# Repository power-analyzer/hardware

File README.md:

# Hardware

This is the hardware and microcontroller software component of Ryan Rabello and Nathan Zimmerly's senior project.

## Getting Started

The PCB folder is a KiCAD project. Once this is done, 

## Prerequisites

KiCAD and PlatformIO using either Visual Studio Code or Atom.

## Authors

Nathan Zimmerly and Ryan Rabello.

## Acknowledgments

OpenEnergyMonitor

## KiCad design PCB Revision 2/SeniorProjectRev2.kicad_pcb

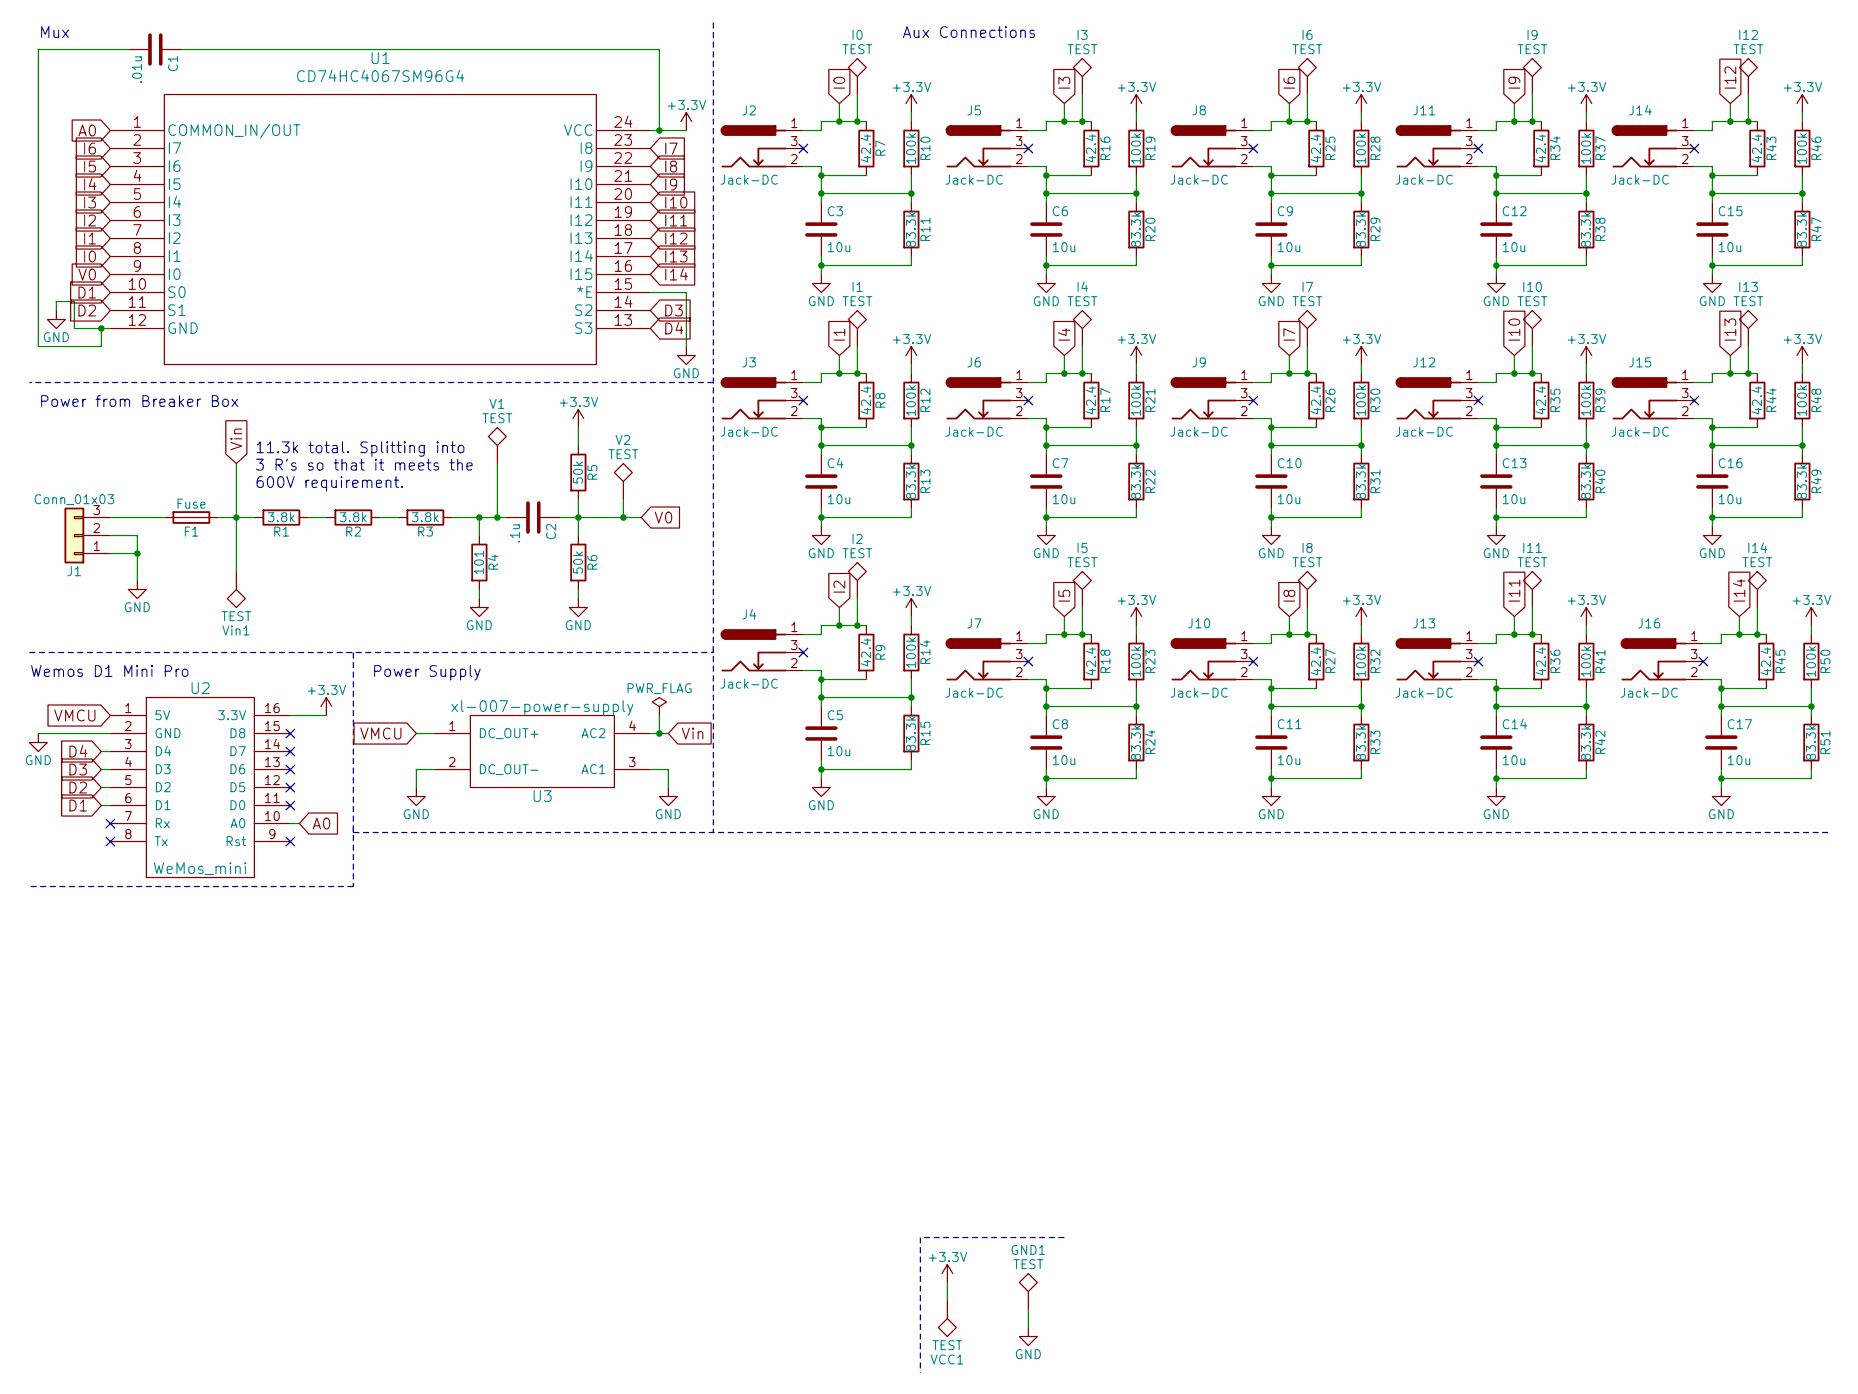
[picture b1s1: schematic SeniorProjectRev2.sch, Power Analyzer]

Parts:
C1: .01u; C_0805
C2: .1u; C_0805
C3, C4, C5, C6, C7, C8, C9, C10, C11, C12, C13, C14, C15, C16, C17: 10u; C_0805
F1: Fuse; fuse-rev2
GND1: TEST; Measurement_Point_Round-TH_Small
I0, I1, I2, I3, I4, I5, I6, I7, I8, I9, I10, I11, I12, I13, I14: TEST; Measurement_Point_Round-TH_Small
J1: Conn_01x03; CONN_TERM_BLOCK
J2, J3, J4, J5, J6, J7, J8, J9, J10, J11, J12, J13, J14, J15, J16: Jack-DC; AUDIO-JACK-TRRS-SMD-2
R1, R2, R3: 3.8k; R_0805
R4: 101; R_0805
R5, R6: 50k; R_0805
R7, R8, R9, R16, R17, R18, R25, R26, R27, R34, R35, R36, R43, R44, R45: 42.4; R_0805
R10, R12, R14, R19, R21, R23, R28, R30, R32, R37, R39, R41, R46, R48, R50: 100k; R_0805
R11, R13, R15, R20, R22, R24, R29, R31, R33, R38, R40, R42, R47, R49, R51: 83.3k; R_0805
U1: CD74HC4067SM96G4; SOIC-24W_7.5x15.4mm_Pitch1.27mm
U2: WeMos_mini; D1_mini_board
U3: xl-007-power-supply; DAOKI-Power-Supply
V1, V2: TEST; Measurement_Point_Round-TH_Small
VCC1: TEST; Measurement_Point_Round-TH_Small
Vin1: TEST; Measurement_Point_Round-TH_Small

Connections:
+3V3: C1.1, R5.1, R10.1, R12.1, R14.1, R19.1, R21.1, R23.1, R28.1, R30.1, R32.1, R37.1, R39.1, R41.1, R46.1, R48.1, R50.1, U1.24 (VCC), U2.16 (3.3V), VCC1.1
A0: U1.1 (COMMON_IN/OUT), U2.10 (A0)
D1: U1.10 (S0), U2.6 (D1)
D2: U1.11 (S1), U2.5 (D2)
D3: U1.14 (S2), U2.4 (D3)
D4: U1.13 (S3), U2.3 (D4)
GND: C1.2, C3.2, C4.2, C5.2, C6.2, C7.2, C8.2, C9.2, C10.2, C11.2, C12.2, C13.2, C14.2, C15.2, C16.2, C17.2, GND1.1, J1.1, J1.2, R4.2, R6.2, R11.2, R13.2, R15.2, R20.2, R22.2, R24.2, R29.2, R31.2, R33.2, R38.2, R40.2, R42.2, R47.2, R49.2, R51.2, U1.12 (GND), U1.15 (*E), U2.2 (GND), U3.2 (DC_OUT-), U3.3 (AC1)
I0: I0.1, J2.1, R7.1, U1.8 (I1)
I1: I1.1, J3.1, R8.1, U1.7 (I2)
I2: I2.1, J4.1, R9.1, U1.6 (I3)
I3: I3.1, J5.1, R16.1, U1.5 (I4)
I4: I4.1, J6.1, R17.1, U1.4 (I5)
I5: I5.1, J7.1, R18.1, U1.3 (I6)
I6: I6.1, J8.1, R25.1, U1.2 (I7)
I7: I7.1, J9.1, R26.1, U1.23 (I8)
I8: I8.1, J10.1, R27.1, U1.22 (I9)
I9: I9.1, J11.1, R34.1, U1.21 (I10)
I10: I10.1, J12.1, R35.1, U1.20 (I11)
I11: I11.1, J13.1, R36.1, U1.19 (I12)
I12: I12.1, J14.1, R43.1, U1.18 (I13)
I13: I13.1, J15.1, R44.1, U1.17 (I14)
I14: I14.1, J16.1, R45.1, U1.16 (I15)
unnamed: C2.2, R3.1, R4.1, V1.1
unnamed: C3.1, J2.2, R7.2, R10.2, R11.1
unnamed: C4.1, J3.2, R8.2, R12.2, R13.1
unnamed: C5.1, J4.2, R9.2, R14.2, R15.1
unnamed: C6.1, J5.2, R16.2, R19.2, R20.1
unnamed: C7.1, J6.2, R17.2, R21.2, R22.1
unnamed: C8.1, J7.2, R18.2, R23.2, R24.1
unnamed: C9.1, J8.2, R25.2, R28.2, R29.1
unnamed: C10.1, J9.2, R26.2, R30.2, R31.1
unnamed: C11.1, J10.2, R27.2, R32.2, R33.1
unnamed: C12.1, J11.2, R34.2, R37.2, R38.1
unnamed: C13.1, J12.2, R35.2, R39.2, R40.1
unnamed: C14.1, J13.2, R36.2, R41.2, R42.1
unnamed: C15.1, J14.2, R43.2, R46.2, R47.1
unnamed: C16.1, J15.2, R44.2, R48.2, R49.1
unnamed: C17.1, J16.2, R45.2, R50.2, R51.1
unnamed: F1.2, J1.3
unnamed: R1.1, R2.2
unnamed: R2.1, R3.2
V0: C2.1, R5.2, R6.1, U1.9 (I0), V2.1
VMCU: U2.1 (5V), U3.1 (DC_OUT+)
Vin: F1.1, R1.2, U3.4 (AC2), Vin1.1

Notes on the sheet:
Mux
Aux Connections
Power from Breaker Box
Power Supply
Wemos D1 Mini Pro
11.3k total. Splitting into 3 R's so that it meets the 600V requirement.

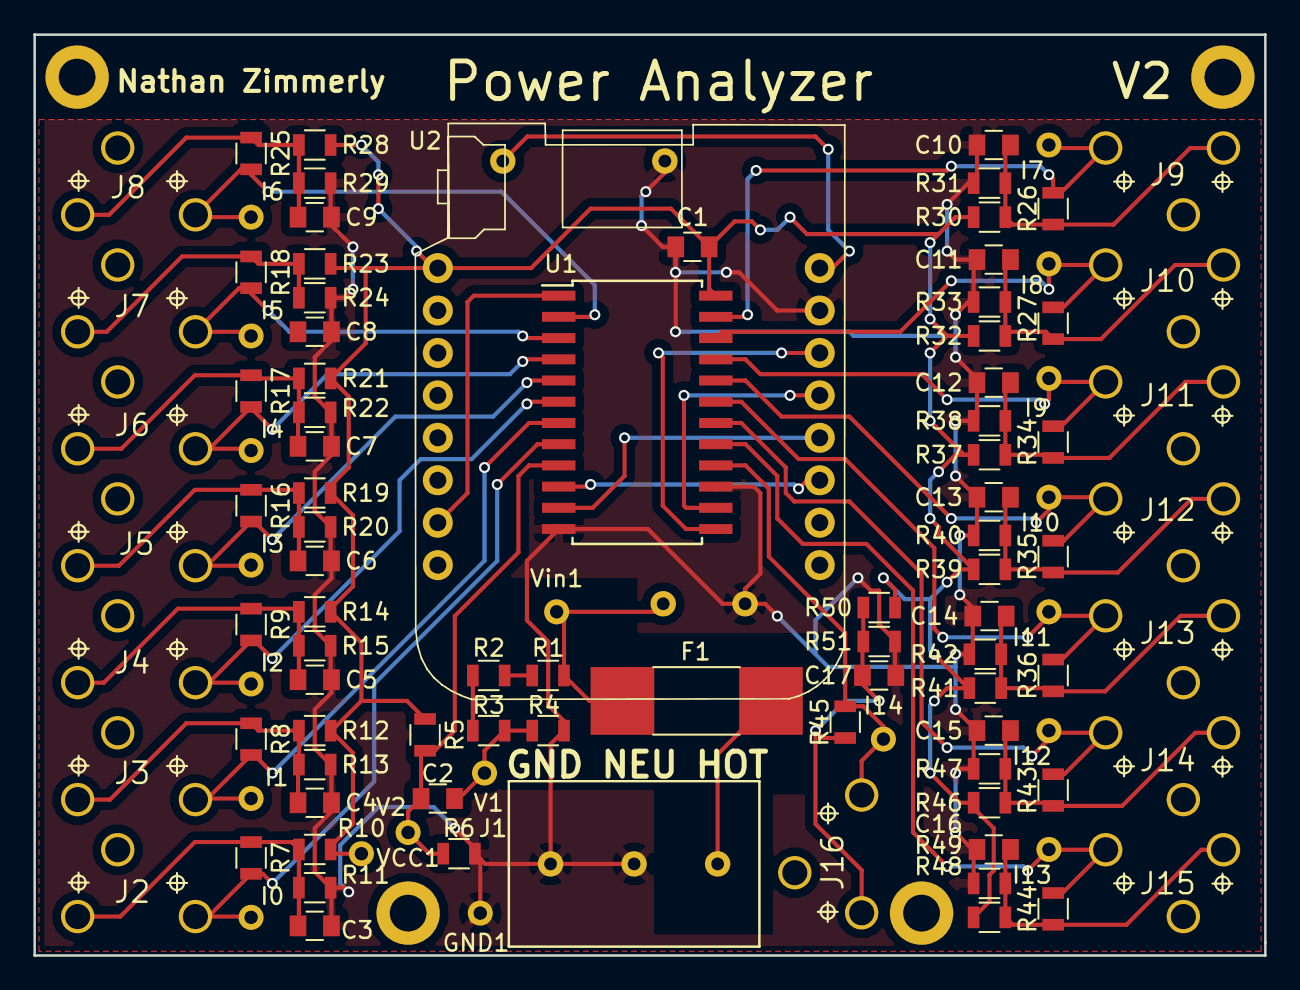
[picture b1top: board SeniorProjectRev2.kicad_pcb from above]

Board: 2 copper layers, 73.7 x 55.1 mm, 108 parts (1 on the bottom side), 44 nets.

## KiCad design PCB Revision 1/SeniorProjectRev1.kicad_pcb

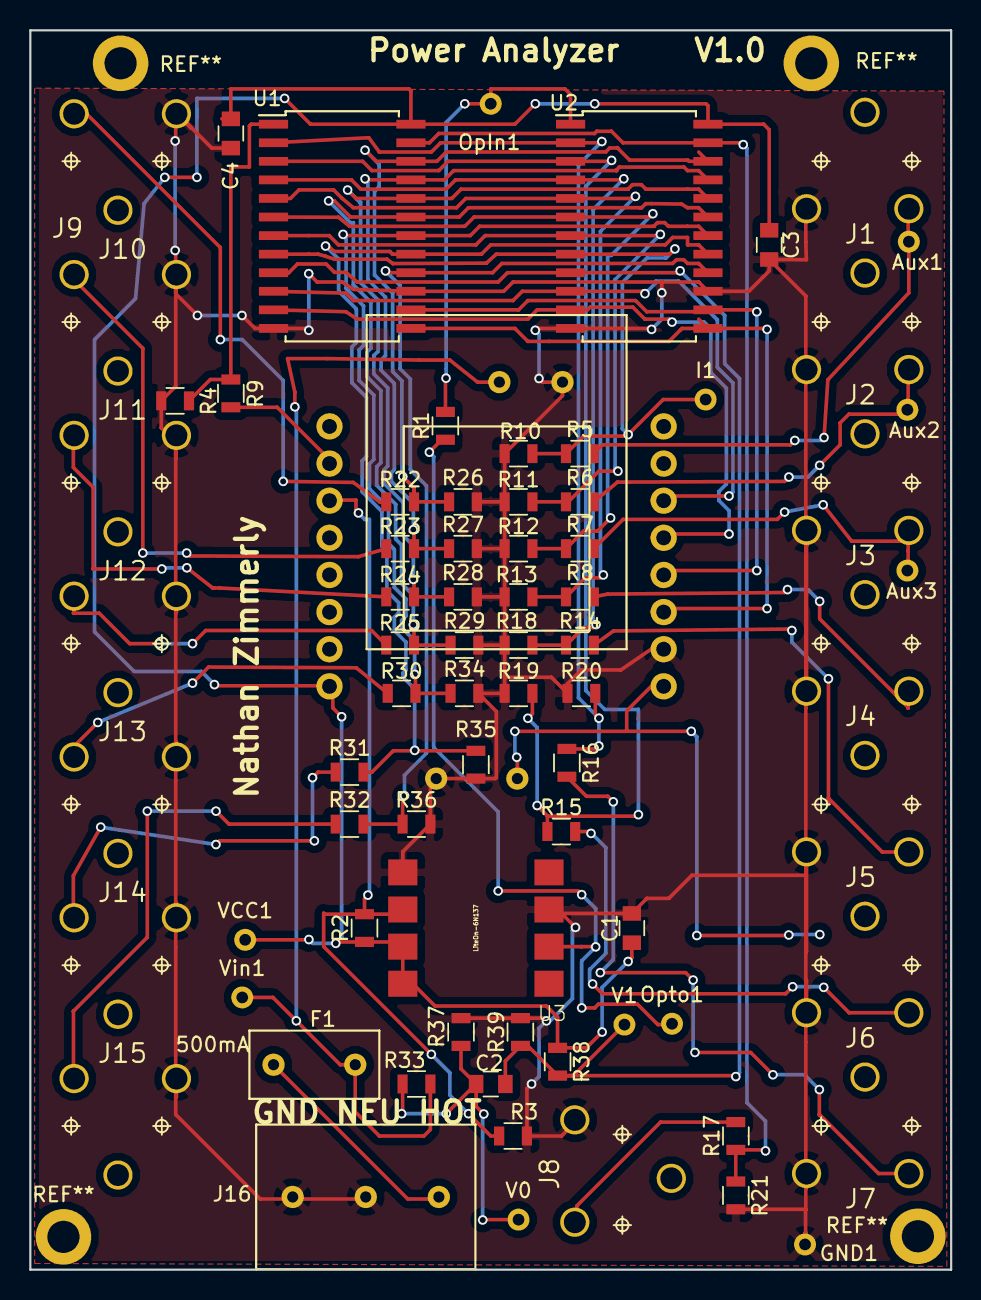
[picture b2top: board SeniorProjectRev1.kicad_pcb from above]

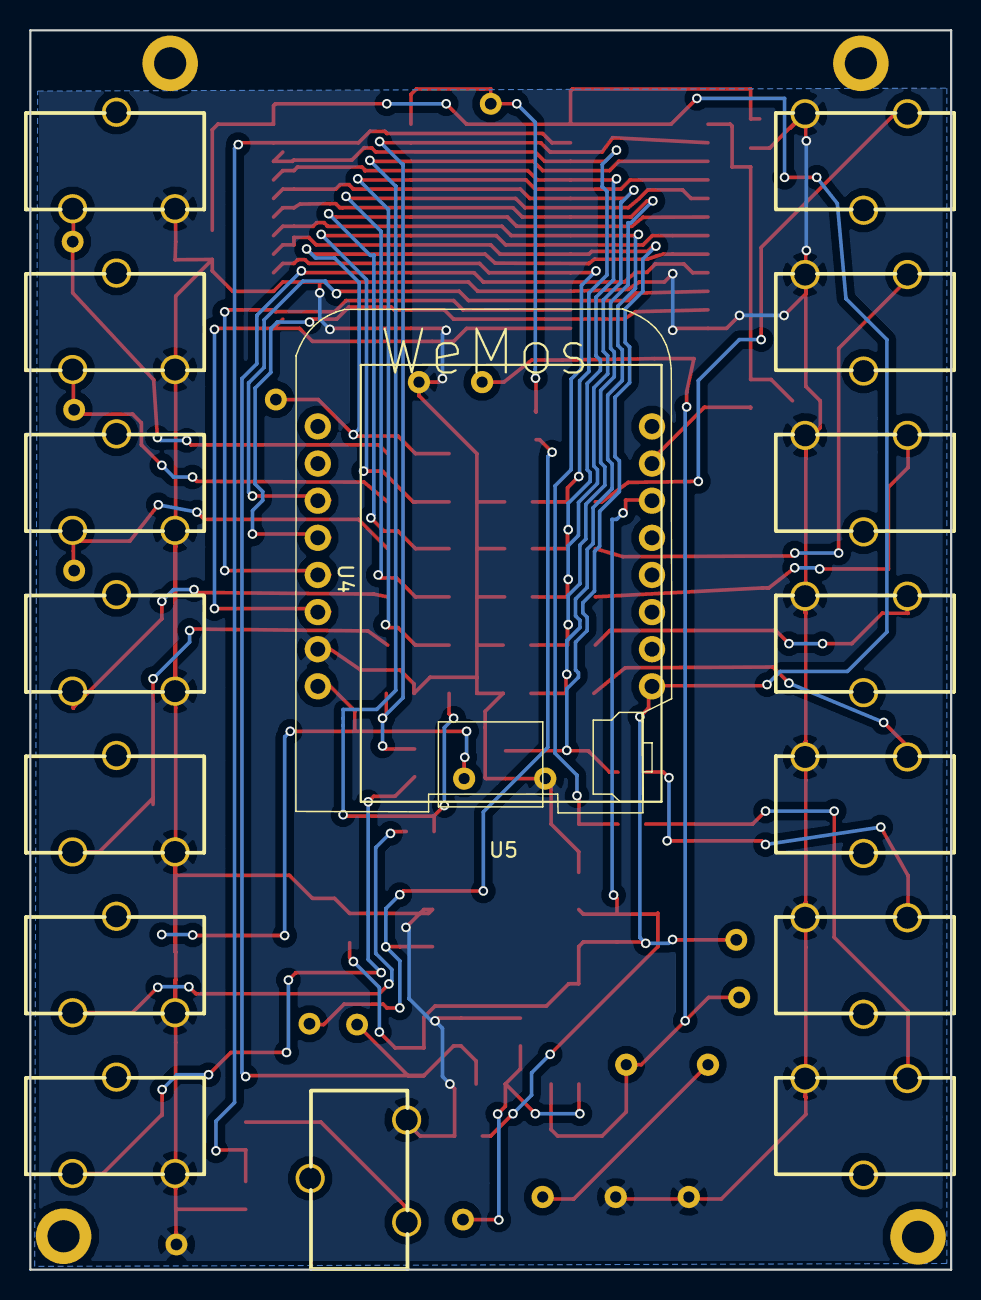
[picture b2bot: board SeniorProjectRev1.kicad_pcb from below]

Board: 2 copper layers, 63.0 x 84.8 mm, 76 parts (2 on the bottom side), 46 nets.

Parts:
Aux1, Aux2, Aux3: TEST; Measurement_Point_Round-TH_Small
C1: .01 uF; C_0805
C2, C3, C4: C; C_0805
F1: Fuse; FUSE-500MA
GND1: TEST; Measurement_Point_Round-TH_Small
I1: TEST; Measurement_Point_Round-TH_Small
J1, J2, J3, J4, J5, J6, J7, J8, J9, J10, J11, J12, J13, J14, J15: Jack-DC; AUDIO-JACK-TRRS-SMD-2
J16: Conn_01x03; CONN_TERM_BLOCK
OpIn1: TEST; Measurement_Point_Round-TH_Small
Opto1: TEST; Measurement_Point_Round-TH_Small
R1, R2, R3, R4, R5, R6, R7, R8, R9, R10, R11, R12, R13, R14, R15, R16, R17, R18, R19, R20, R21, R22, R23, R24, R25, R26, R27, R28, R29, R30, R31, R32, R33, R34, R35, R36, R37, R38, R39: R; R_0805
U1, U2: CD74HC4067SM96G4; SOIC-24W_7.5x15.4mm_Pitch1.27mm
U3: LiteOn-6N137; SMD-8
U4: xl-007-power-supply; Power-Supply
U5: WeMos_mini; D1_mini_board
V0, V1: TEST; Measurement_Point_Round-TH_Small
VCC1: TEST; Measurement_Point_Round-TH_Small
Vin1: TEST; Measurement_Point_Round-TH_Small

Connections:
+3V3: C1.1, C3.1, C4.1, R2.1, R38.1, U1.24, U2.24, U3.7, U3.8, U5.16, VCC1.1
A0: R9.1, U5.10
D0: R2.2, R3.1, U3.6, U5.11
D1: U1.10, U2.10, U5.6
D2: U1.11, U2.11, U5.5
D3: U1.14, U2.14, U5.4
D4: U1.13, U2.13, U5.3
GND: C1.2, C3.2, C4.2, GND1.1, J1.1, J2.1, J3.1, J4.1, J5.1, J6.1, J7.1, J8.1, J9.1, J10.1, J11.1, J12.1, J13.1, J14.1, J15.1, J16.1, J16.2, R3.2, R4.2, R10.2, R11.2, R12.2, R13.2, R18.2, R19.2, R20.2, R21.2, R26.2, R27.2, R28.2, R29.2, R34.2, R35.2, R36.2, R37.2, R39.2, U1.12, U1.15, U2.12, U2.15, U3.3, U3.5, U4.2, U4.3, U5.2
I0: I1.1, R5.1, R10.1, U1.8, U2.8
I1: R6.1, R11.1, U1.7, U2.7
I2: R7.1, R12.1, U1.6, U2.6
I3: R8.1, R13.1, U1.5, U2.5
I4: R14.1, R18.1, U1.4, U2.4
I5: R15.1, R19.1, U1.3, U2.3
I6: R16.1, R20.1, U1.2, U2.2
I7: R17.1, R21.1, U1.23, U2.23
I8: R22.1, R26.1, U1.22, U2.22
I9: R23.1, R27.1, U1.21, U2.21
I10: R24.1, R28.1, U1.20, U2.20
I11: R25.1, R29.1, U1.19, U2.19
I12: R30.1, R34.1, U1.18, U2.18
I13: R31.1, R35.1, U1.17, U2.17
I14: R32.1, R36.1, U1.16, U2.16
unnamed: Aux1.1, J1.2, R5.2
unnamed: Aux2.1, J2.2, R6.2
unnamed: Aux3.1, J3.2, R7.2
unnamed: C2.2, R33.1, R37.1, V0.1
unnamed: F1.2, J16.3
unnamed: J4.2, R8.2
unnamed: J5.2, R14.2
unnamed: J6.2, R15.2
unnamed: J7.2, R16.2
unnamed: J8.2, R17.2
unnamed: J9.2, R22.2
unnamed: J10.2, R23.2
unnamed: J11.2, R24.2
unnamed: J12.2, R25.2
unnamed: J13.2, R30.2
unnamed: J14.2, R31.2
unnamed: J15.2, R32.2
unnamed: Opto1.1, R1.1, U3.2
OptoIn: OpIn1.1, R1.2, U2.1
ToA0: R4.1, R9.2, U1.1
V0: C2.1, R38.2, R39.1, U1.9, U2.9, V1.1
VMCU: U4.1, U5.1
Vin: F1.1, R33.2, U4.4, Vin1.1

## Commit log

2018-06-01 1st Rev of PCB
2018-06-01 Testing data and calculations for the hardware
2018-06-01 Added project and test software for the microcontroller
2018-06-01 Update README.md
    Updated hardware readme with minimal information.
2018-06-01 Added gerber files for printing the PCB
2018-06-01 Started 2nd Rev of PCB
2018-06-04 Updated current and voltage conversions and updated JSON library for micrcontroller
2018-06-06 Finished Rev 2
2018-06-06 Update README.md
    fixed lower case H.
2018-06-07 updated software
2018-06-11 Updated calculations with error
